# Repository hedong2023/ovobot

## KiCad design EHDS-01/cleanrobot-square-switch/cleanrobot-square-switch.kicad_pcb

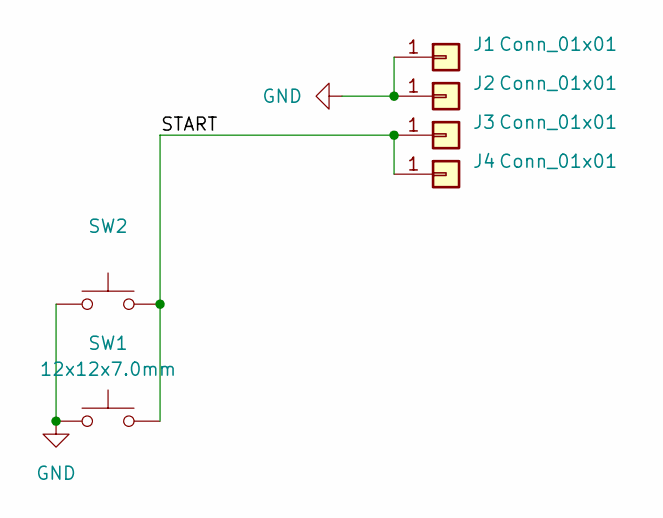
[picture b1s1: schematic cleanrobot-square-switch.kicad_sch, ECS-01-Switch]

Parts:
J1, J2, J3, J4: Conn_01x01; SolderWire-0.5sqmm_1x01_D0.9mm_OD2.1mm
SW1: 12x12x7.0mm; SW_PUSH-12mm
SW2: (no value)

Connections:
/START: J3.1, J4.1, SW1.2, SW2.2
GND: J1.1, J2.1, SW1.1, SW2.1

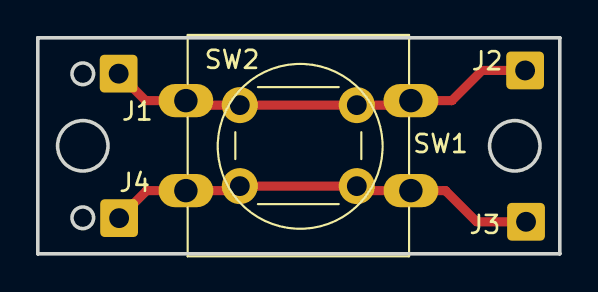
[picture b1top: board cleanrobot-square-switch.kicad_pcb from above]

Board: 2 copper layers, 29.0 x 12.0 mm, 6 parts (0 on the bottom side), 2 nets.

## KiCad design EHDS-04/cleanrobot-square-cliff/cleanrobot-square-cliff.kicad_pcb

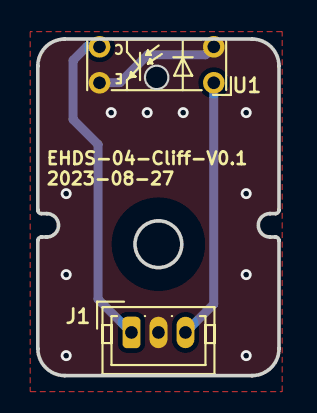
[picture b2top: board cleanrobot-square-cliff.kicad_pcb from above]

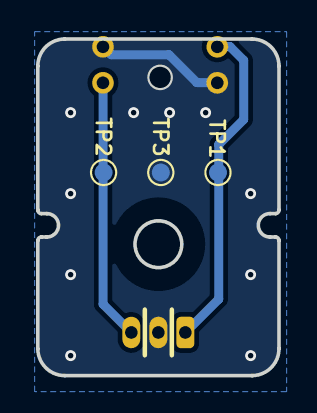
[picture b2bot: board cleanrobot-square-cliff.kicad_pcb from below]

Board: 2 copper layers, 13.4 x 18.7 mm, 5 parts (3 on the bottom side), 3 nets.

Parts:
J1: ZH1.5MM/3ASMT; JST_ZH_B03B-ZR_1x03_P1.50mm_Vertical
TP1: EDGE_DET_LT; TestPoint_Pad_D1.0mm
TP2: EDGE_DET_OUT; TestPoint_Pad_D1.0mm
TP3: GND; TestPoint_Pad_D1.0mm
U1: ITR1203; EverLight_ITR1203_7.5x2.6mm_P2.0mm

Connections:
/EDGE_DET_LT: J1.1, TP1.1, U1.3 (C)
GND: J1.2, TP3.1, U1.2 (K), U1.4 (E)
unnamed: J1.3, TP2.1, U1.1 (A)

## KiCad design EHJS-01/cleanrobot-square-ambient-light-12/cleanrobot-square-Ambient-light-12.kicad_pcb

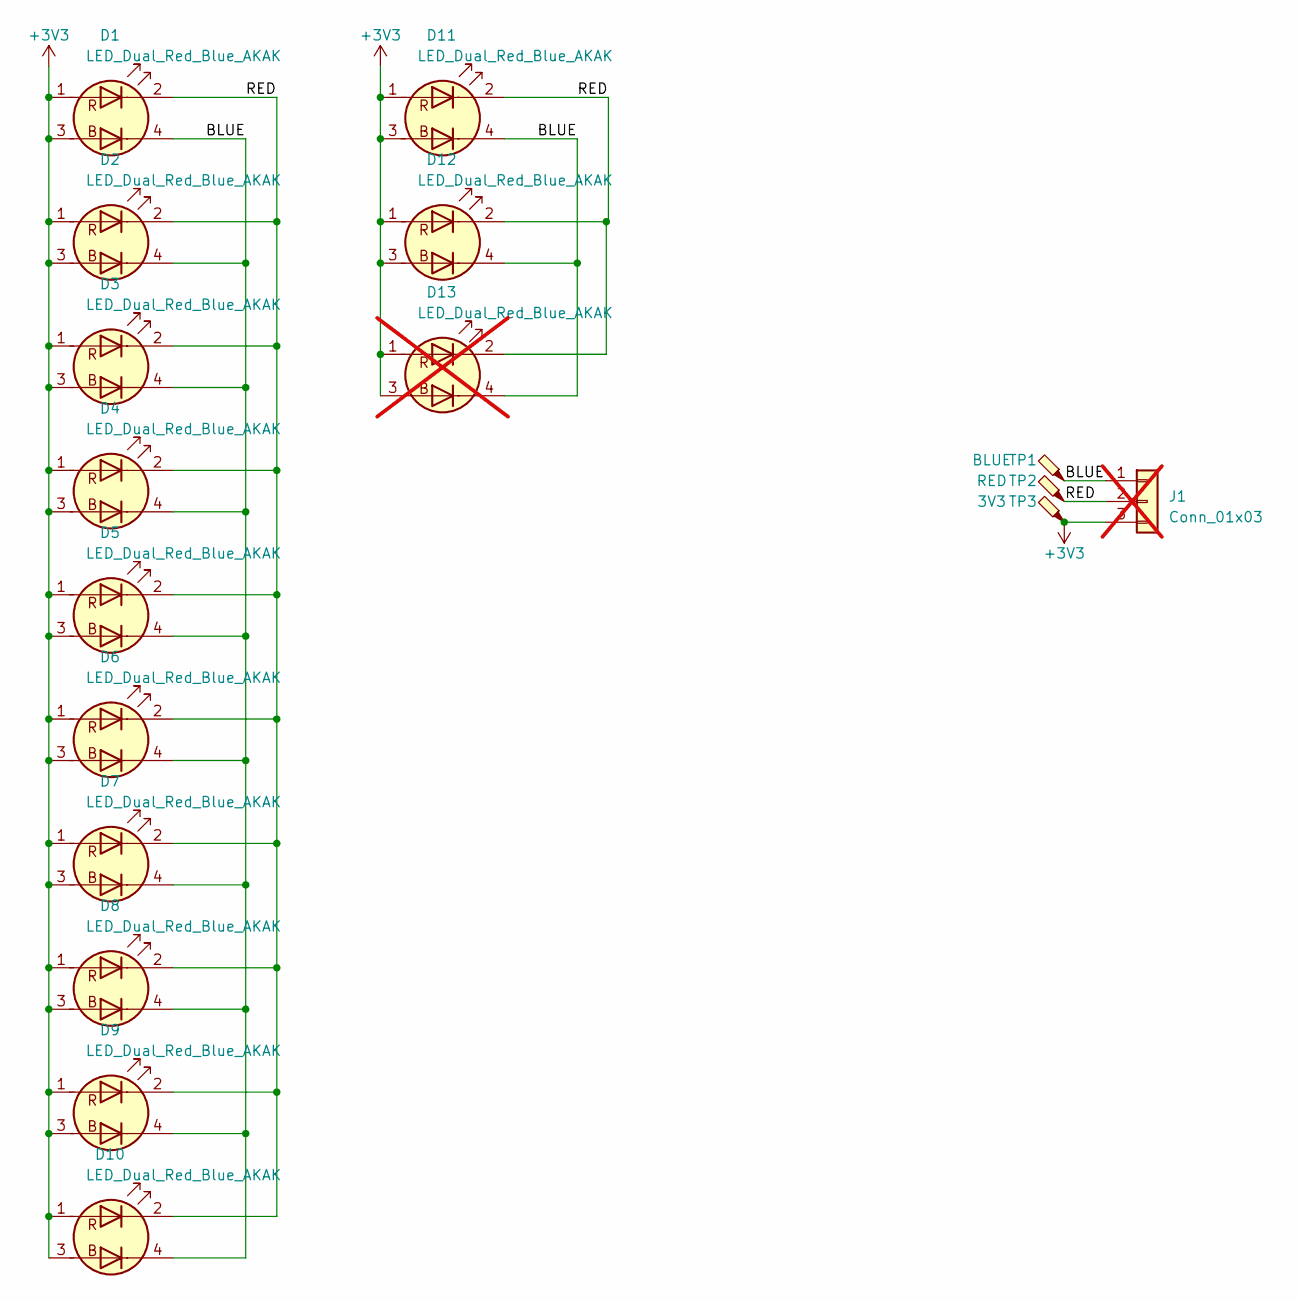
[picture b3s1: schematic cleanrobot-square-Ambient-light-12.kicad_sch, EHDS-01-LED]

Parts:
D1, D2, D3, D4, D5, D6, D7, D8, D9, D10, D11, D12: LED_Dual_Red_Blue_AKAK; LED_Dual_1.6x1.5mm
D13: LED_Dual_Red_Blue_AKAK; LED_Dual_1.6x1.5mm; not fitted
J1: Conn_01x03; Pad_THTPad_3x1.3mmx3; not fitted
TP1: BLUE; TestPoint_Pad_D1.0mm
TP2: RED; TestPoint_Pad_D1.0mm
TP3: 3V3; TestPoint_Pad_D1.0mm

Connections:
+3V3: D1.1 (A1), D1.3 (A2), D2.1 (A1), D2.3 (A2), D3.1 (A1), D3.3 (A2), D4.1 (A1), D4.3 (A2), D5.1 (A1), D5.3 (A2), D6.1 (A1), D6.3 (A2), D7.1 (A1), D7.3 (A2), D8.1 (A1), D8.3 (A2), D9.1 (A1), D9.3 (A2), D10.1 (A1), D10.3 (A2), D11.1 (A1), D11.3 (A2), D12.1 (A1), D12.3 (A2), D13.1 (A1), D13.3 (A2), J1.3, TP3.1
/BLUE: D1.4 (K2), D2.4 (K2), D3.4 (K2), D4.4 (K2), D5.4 (K2), D6.4 (K2), D7.4 (K2), D8.4 (K2), D9.4 (K2), D10.4 (K2), D11.4 (K2), D12.4 (K2), D13.4 (K2), J1.1, TP1.1
/RED: D1.2 (K1), D2.2 (K1), D3.2 (K1), D4.2 (K1), D5.2 (K1), D6.2 (K1), D7.2 (K1), D8.2 (K1), D9.2 (K1), D10.2 (K1), D11.2 (K1), D12.2 (K1), D13.2 (K1), J1.2, TP2.1

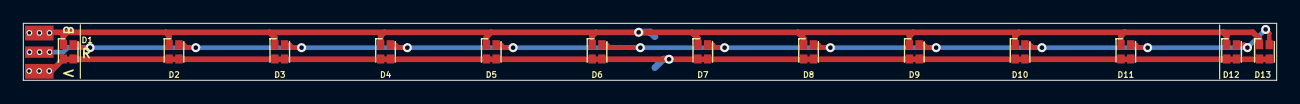
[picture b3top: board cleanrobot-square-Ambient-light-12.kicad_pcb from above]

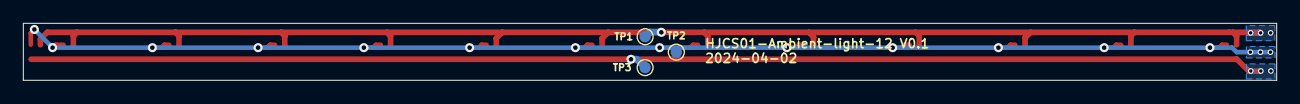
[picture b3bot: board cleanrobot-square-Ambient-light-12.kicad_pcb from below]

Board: 2 copper layers, 110.0 x 5.0 mm, 17 parts (3 on the bottom side), 3 nets.

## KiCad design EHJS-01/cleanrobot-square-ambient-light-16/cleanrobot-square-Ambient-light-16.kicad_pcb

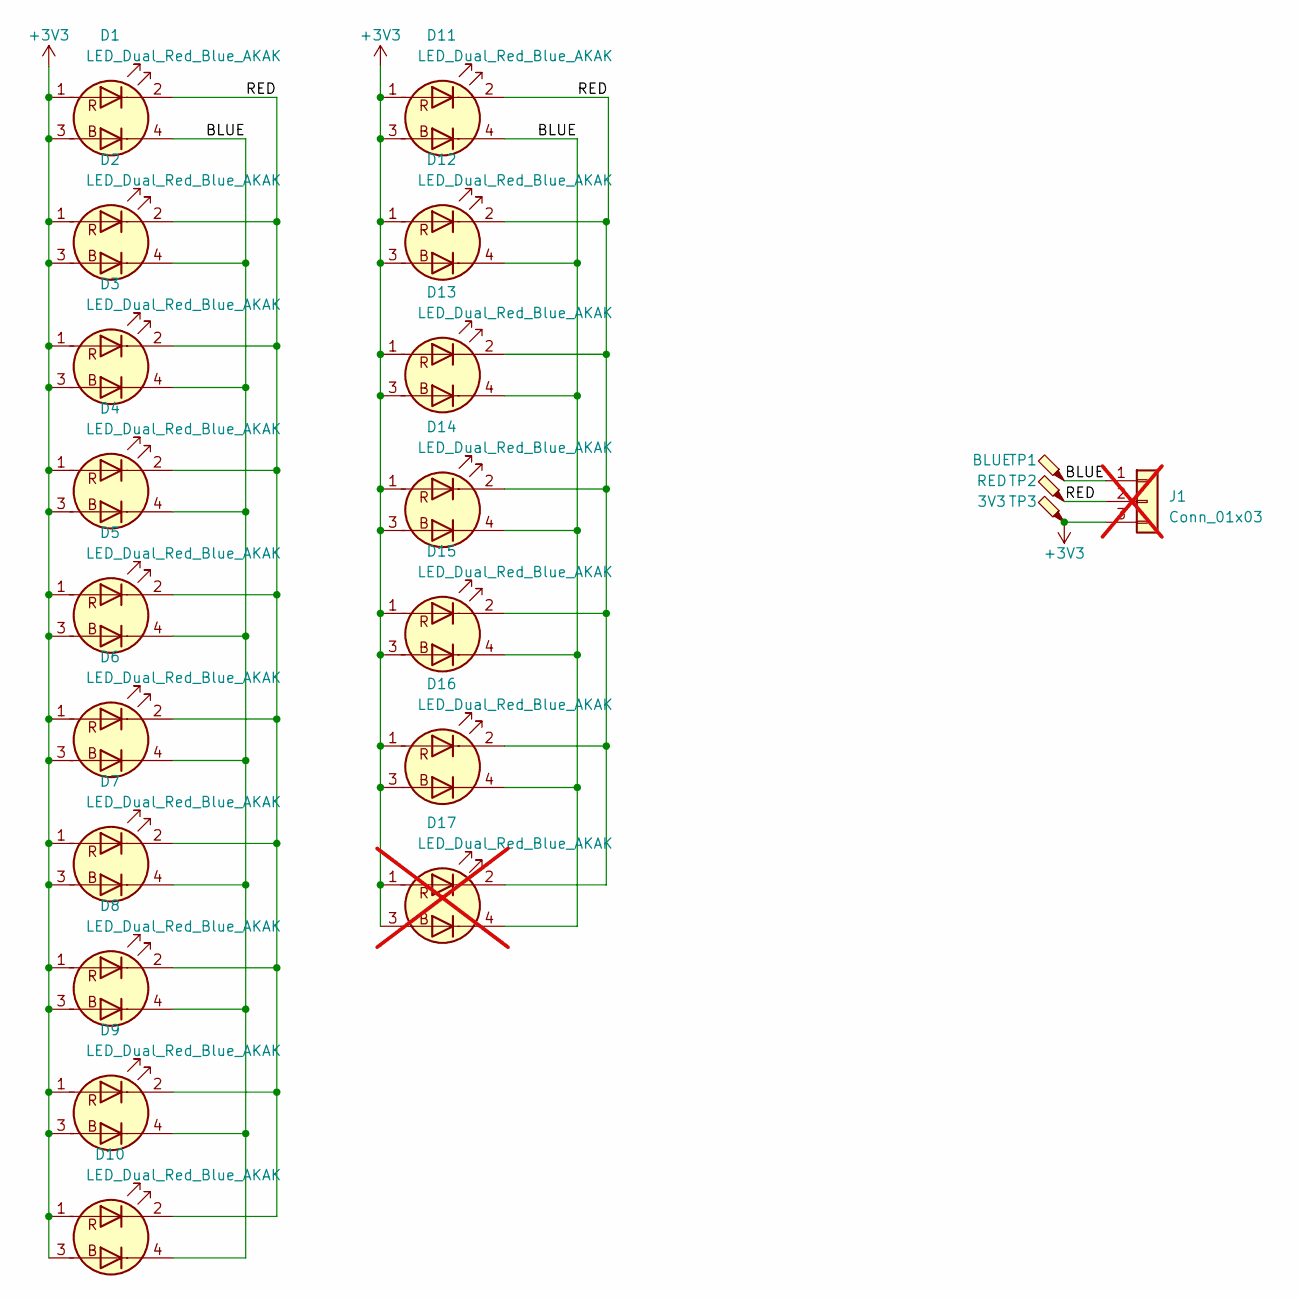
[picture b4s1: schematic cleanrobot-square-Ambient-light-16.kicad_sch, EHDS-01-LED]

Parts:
D1, D2, D3, D4, D5, D6, D7, D8, D9, D10, D11, D12, D13, D14, D15, D16: LED_Dual_Red_Blue_AKAK; LED_Dual_1.6x1.5mm
D17: LED_Dual_Red_Blue_AKAK; LED_Dual_1.6x1.5mm; not fitted
J1: Conn_01x03; Pad_THTPad_3x1.3mmx3; not fitted
TP1: BLUE; TestPoint_Pad_D1.0mm
TP2: RED; TestPoint_Pad_D1.0mm
TP3: 3V3; TestPoint_Pad_D1.0mm

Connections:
+3V3: D1.1 (A1), D1.3 (A2), D2.1 (A1), D2.3 (A2), D3.1 (A1), D3.3 (A2), D4.1 (A1), D4.3 (A2), D5.1 (A1), D5.3 (A2), D6.1 (A1), D6.3 (A2), D7.1 (A1), D7.3 (A2), D8.1 (A1), D8.3 (A2), D9.1 (A1), D9.3 (A2), D10.1 (A1), D10.3 (A2), D11.1 (A1), D11.3 (A2), D12.1 (A1), D12.3 (A2), D13.1 (A1), D13.3 (A2), D14.1 (A1), D14.3 (A2), D15.1 (A1), D15.3 (A2), D16.1 (A1), D16.3 (A2), D17.1 (A1), D17.3 (A2), J1.3, TP3.1
/BLUE: D1.4 (K2), D2.4 (K2), D3.4 (K2), D4.4 (K2), D5.4 (K2), D6.4 (K2), D7.4 (K2), D8.4 (K2), D9.4 (K2), D10.4 (K2), D11.4 (K2), D12.4 (K2), D13.4 (K2), D14.4 (K2), D15.4 (K2), D16.4 (K2), D17.4 (K2), J1.1, TP1.1
/RED: D1.2 (K1), D2.2 (K1), D3.2 (K1), D4.2 (K1), D5.2 (K1), D6.2 (K1), D7.2 (K1), D8.2 (K1), D9.2 (K1), D10.2 (K1), D11.2 (K1), D12.2 (K1), D13.2 (K1), D14.2 (K1), D15.2 (K1), D16.2 (K1), D17.2 (K1), J1.2, TP2.1

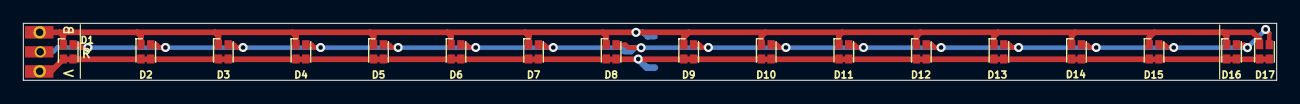
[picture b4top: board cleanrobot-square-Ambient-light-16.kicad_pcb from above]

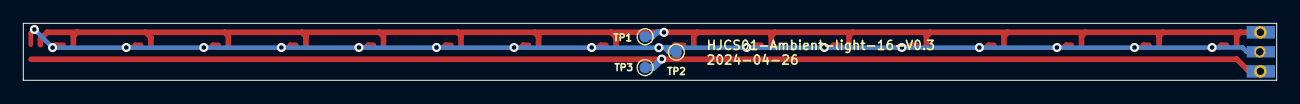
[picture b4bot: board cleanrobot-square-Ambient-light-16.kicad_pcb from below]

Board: 2 copper layers, 110.0 x 5.0 mm, 21 parts (3 on the bottom side), 3 nets.

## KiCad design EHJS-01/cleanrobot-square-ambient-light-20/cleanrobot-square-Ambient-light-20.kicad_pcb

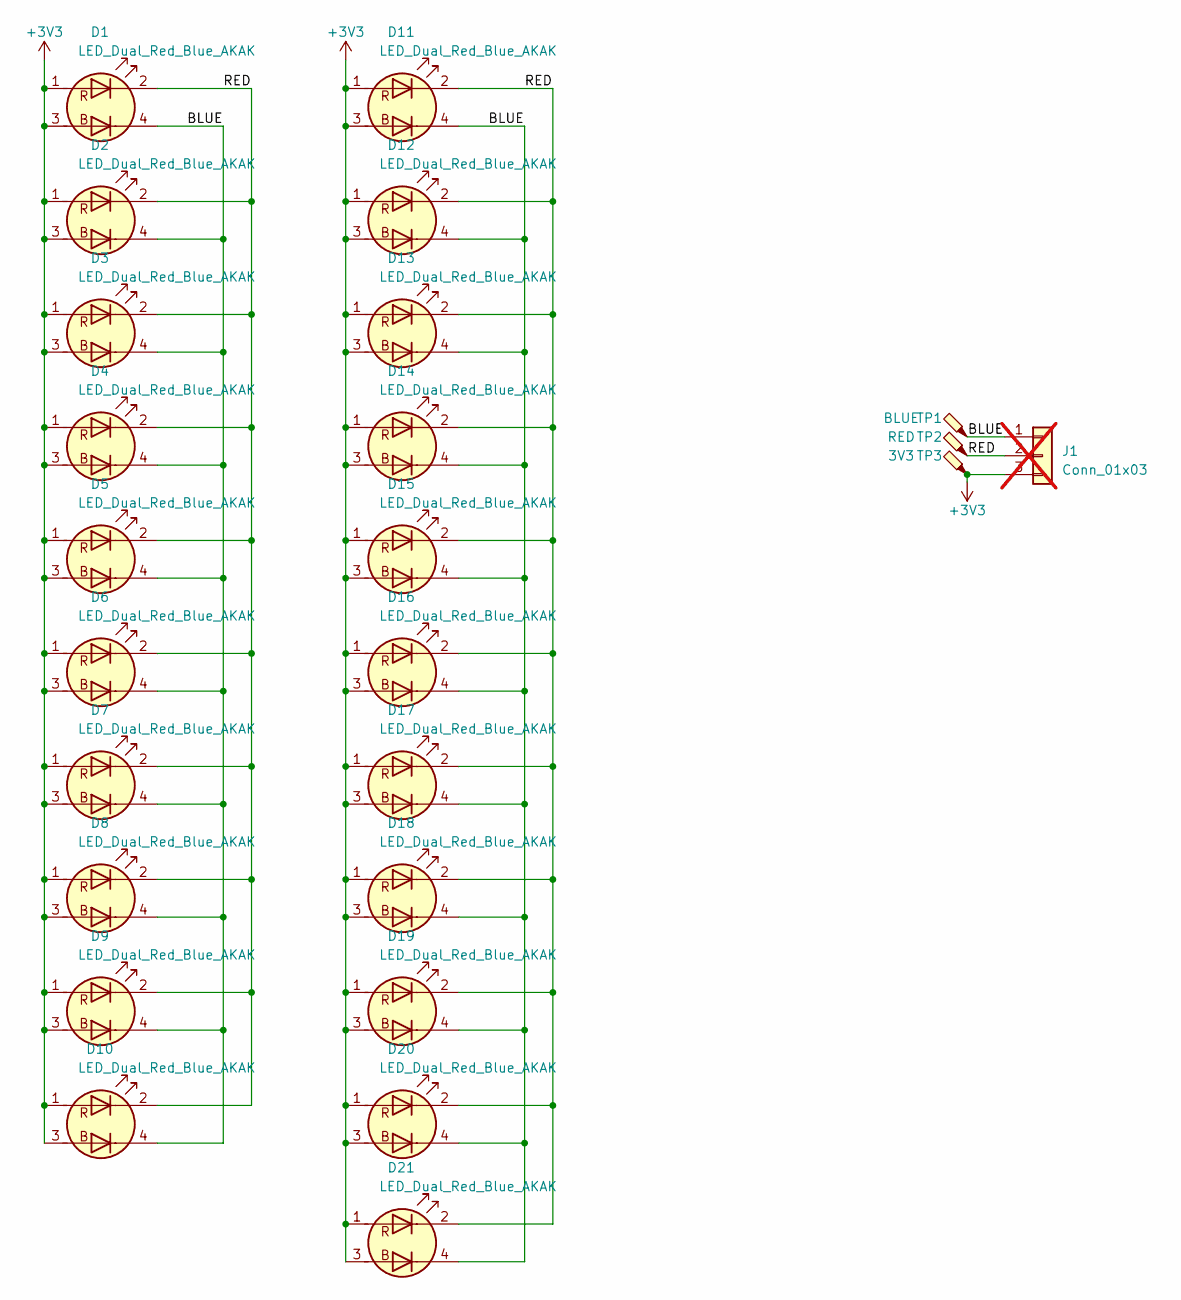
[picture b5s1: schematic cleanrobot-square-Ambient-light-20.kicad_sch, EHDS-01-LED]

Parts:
D1, D2, D3, D4, D5, D6, D7, D8, D9, D10, D11, D12, D13, D14, D15, D16, D17, D18, D19, D20, D21: LED_Dual_Red_Blue_AKAK; LED_Dual_1.6x1.5mm
J1: Conn_01x03; Pad_THTPad_3x1.3mmx3; not fitted
TP1: BLUE; TestPoint_Pad_D1.0mm
TP2: RED; TestPoint_Pad_D1.0mm
TP3: 3V3; TestPoint_Pad_D1.0mm

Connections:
+3V3: D1.1 (A1), D1.3 (A2), D2.1 (A1), D2.3 (A2), D3.1 (A1), D3.3 (A2), D4.1 (A1), D4.3 (A2), D5.1 (A1), D5.3 (A2), D6.1 (A1), D6.3 (A2), D7.1 (A1), D7.3 (A2), D8.1 (A1), D8.3 (A2), D9.1 (A1), D9.3 (A2), D10.1 (A1), D10.3 (A2), D11.1 (A1), D11.3 (A2), D12.1 (A1), D12.3 (A2), D13.1 (A1), D13.3 (A2), D14.1 (A1), D14.3 (A2), D15.1 (A1), D15.3 (A2), D16.1 (A1), D16.3 (A2), D17.1 (A1), D17.3 (A2), D18.1 (A1), D18.3 (A2), D19.1 (A1), D19.3 (A2), D20.1 (A1), D20.3 (A2), D21.1 (A1), D21.3 (A2), J1.3, TP3.1
/BLUE: D1.4 (K2), D2.4 (K2), D3.4 (K2), D4.4 (K2), D5.4 (K2), D6.4 (K2), D7.4 (K2), D8.4 (K2), D9.4 (K2), D10.4 (K2), D11.4 (K2), D12.4 (K2), D13.4 (K2), D14.4 (K2), D15.4 (K2), D16.4 (K2), D17.4 (K2), D18.4 (K2), D19.4 (K2), D20.4 (K2), D21.4 (K2), J1.1, TP1.1
/RED: D1.2 (K1), D2.2 (K1), D3.2 (K1), D4.2 (K1), D5.2 (K1), D6.2 (K1), D7.2 (K1), D8.2 (K1), D9.2 (K1), D10.2 (K1), D11.2 (K1), D12.2 (K1), D13.2 (K1), D14.2 (K1), D15.2 (K1), D16.2 (K1), D17.2 (K1), D18.2 (K1), D19.2 (K1), D20.2 (K1), D21.2 (K1), J1.2, TP2.1

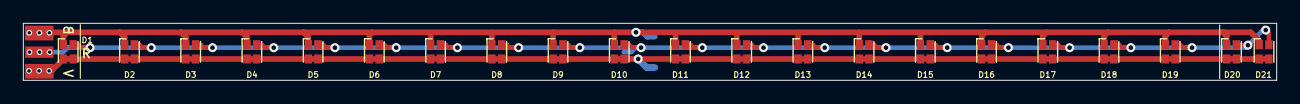
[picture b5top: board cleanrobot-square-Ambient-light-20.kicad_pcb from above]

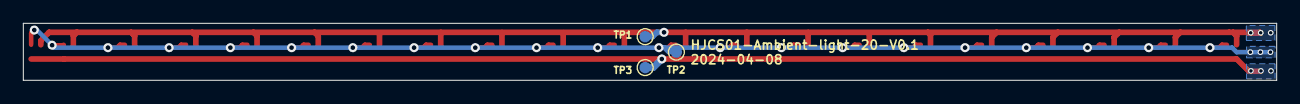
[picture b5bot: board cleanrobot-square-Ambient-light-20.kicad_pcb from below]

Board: 2 copper layers, 110.0 x 5.0 mm, 25 parts (3 on the bottom side), 3 nets.

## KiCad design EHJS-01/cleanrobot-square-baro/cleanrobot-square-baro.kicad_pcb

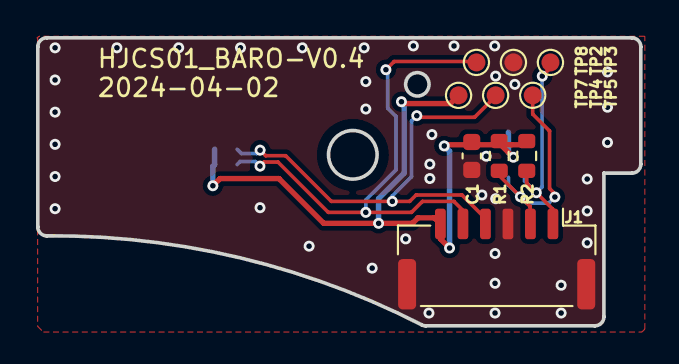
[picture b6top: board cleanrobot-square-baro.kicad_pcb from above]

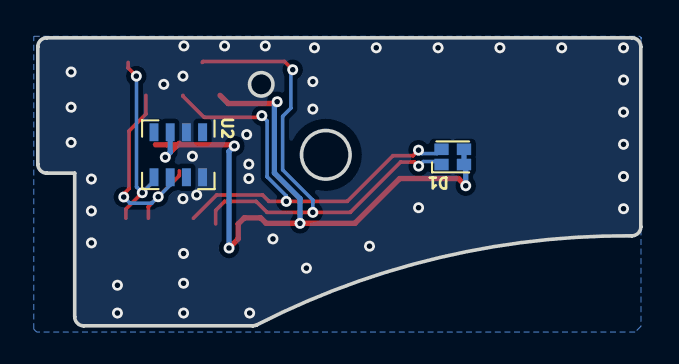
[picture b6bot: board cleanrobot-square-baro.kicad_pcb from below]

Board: 2 copper layers, 33.5 x 16.0 mm, 12 parts (2 on the bottom side), 6 nets.

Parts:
C1: 4.7uF; C_0603_1608Metric
D1: LED_Dual_Red_Blue_AKAK; LED_Dual_1.6x1.5mm
J1: GH1.25MM/6ASMT; JST_GH_BM06B-GHS-TBT_1x06-1MP_P1.25mm_Vertical
R1, R2: 10K/1%; R_0603_1608Metric
TP2: GND; TestPoint_Pad_D1.0mm
TP3: SCL; TestPoint_Pad_D1.0mm
TP4: RED; TestPoint_Pad_D1.0mm
TP5: SDA; TestPoint_Pad_D1.0mm
TP7: 3V3; TestPoint_Pad_D1.0mm
TP8: BLUE; TestPoint_Pad_D1.0mm
U2: HP203B; HOPERF_LGA-8_3.8x3.6mm_P0.9mm

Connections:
+3V3: C1.1, D1.1 (A1), D1.3 (A2), J1.6, R1.1, R2.1, TP7.1, U2.3 (VDD)
/BLUE: D1.4 (K2), J1.5, TP8.1
/RED: D1.2 (K1), J1.4, TP4.1
/SCL1: J1.1, R2.2, TP3.1, U2.5 (SCL)
/SDA1: J1.2, R1.2, TP5.1, U2.6 (SDA)
GND: C1.2, J1.3, J1.MP (MountPin), TP2.1, U2.2 (GND), U2.8 (CSB)
